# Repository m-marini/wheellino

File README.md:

Wheelly is a wheels robot.

The robot consits of

- Chassis with two lateral wheels driven by 2 x DC motors and a free wheel.
- 2 x IR speed sensors for the wheels
- Motor controller board L298N
- 12V DC rechargable motors Li battery
- 5V DC rechargable controller Li battery
- Power supply module 3.3V
- MPU6050 gyroscope module
- ESP32 Vroom main controller board
- SG90 Microservo
- 2 x Lidar sensors
- 6 x microswitch contact sensors
- LCD Display
- Wifi-Camera

The ESP32 controller is driving all the units to allow the robot to collect the sensor data, compute the position relative the initial state, drive the proxcimity sensor direction, drive the robot for a specific direction and speed by feeding back from gyroscpe and speed sensors and comunicate with remote server via wifi sending status and receiving commands.

Documentation in [Wiki](https://github.com/m-marini/wheellino/wiki)

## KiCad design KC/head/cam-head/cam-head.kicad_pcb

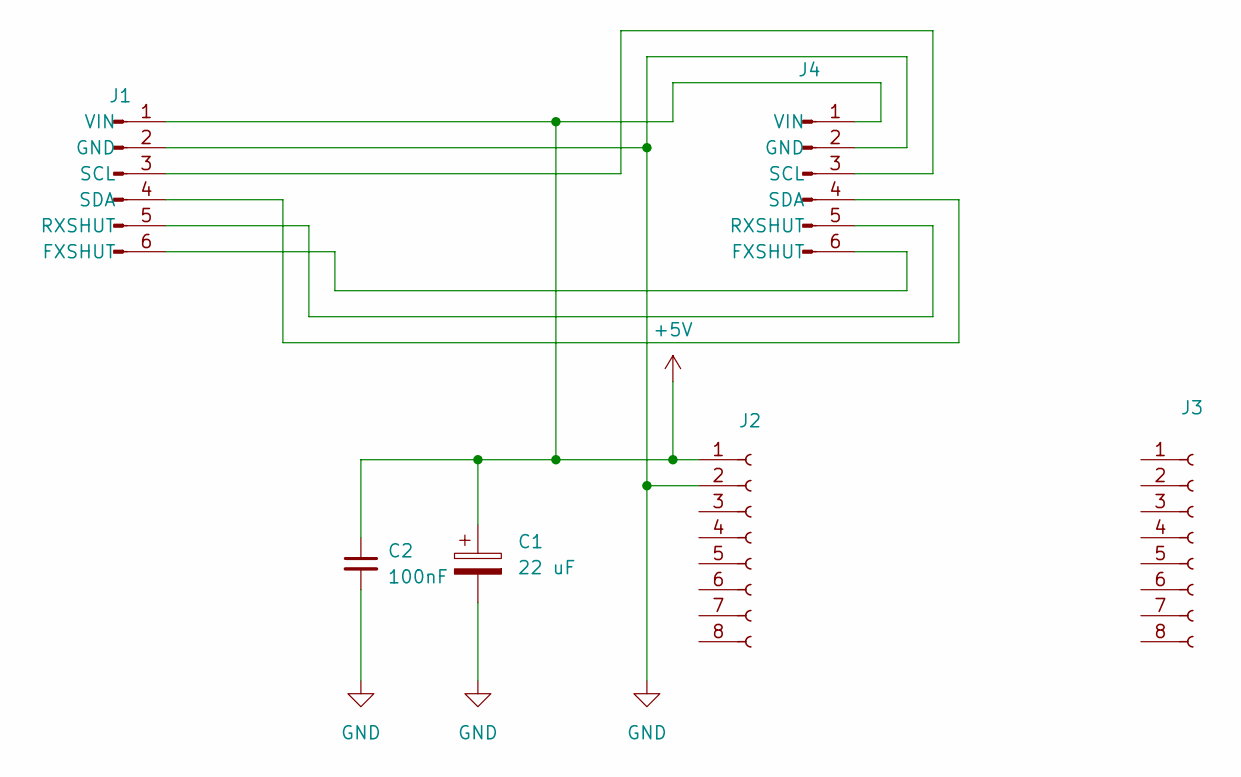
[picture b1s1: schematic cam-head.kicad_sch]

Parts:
C1: 22 uF; CP_Radial_D5.0mm_P2.50mm
C2: 100nF; C_Rect_L7.0mm_W2.5mm_P5.00mm
J1: Conn_01x06_Pin; PinHeader_1x06_P2.54mm_Horizontal
J2, J3: Conn_01x08_Socket; PinSocket_1x08_P2.54mm_Vertical
J4: Conn_01x06_Pin; PinHeader_1x06_P2.54mm_Vertical

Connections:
+5V: C1.1, C2.1, J1.1 (VIN), J2.1, J4.1 (VIN)
GND: C1.2, C2.2, J1.2 (GND), J2.2, J4.2 (GND)
unnamed: J1.6 (FXSHUT), J4.6 (FXSHUT)
unnamed: J1.5 (RXSHUT), J4.5 (RXSHUT)
unnamed: J1.3 (SCL), J4.3 (SCL)
unnamed: J1.4 (SDA), J4.4 (SDA)

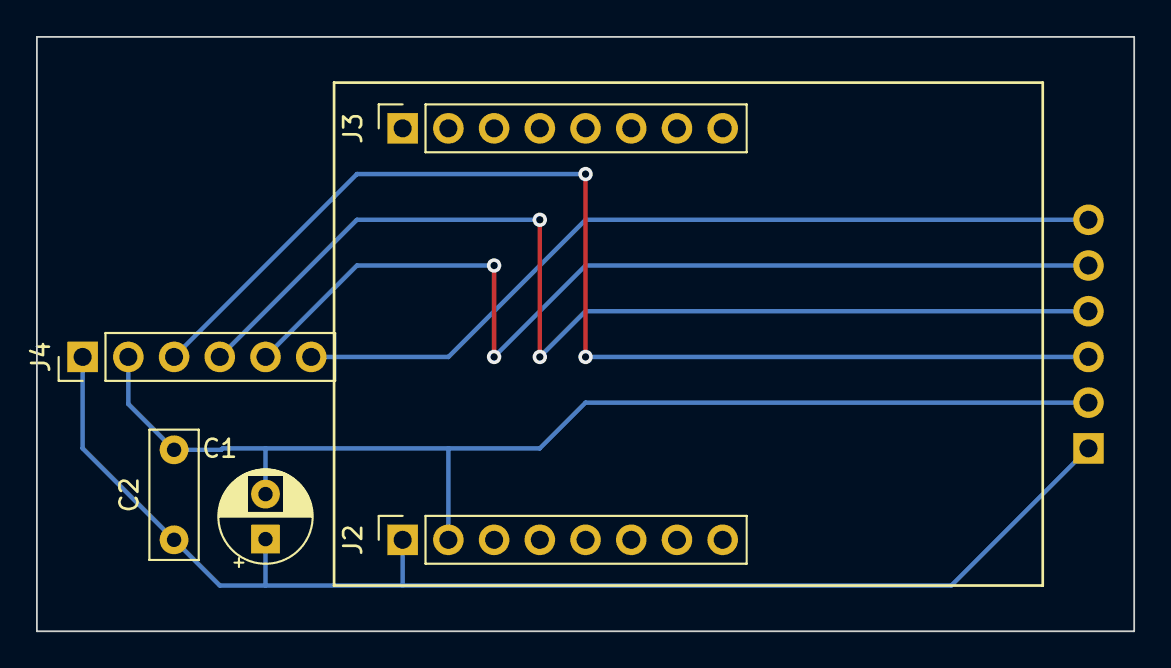
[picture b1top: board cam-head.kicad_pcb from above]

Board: 2 copper layers, 61.0 x 33.0 mm, 6 parts (1 on the bottom side), 6 nets.

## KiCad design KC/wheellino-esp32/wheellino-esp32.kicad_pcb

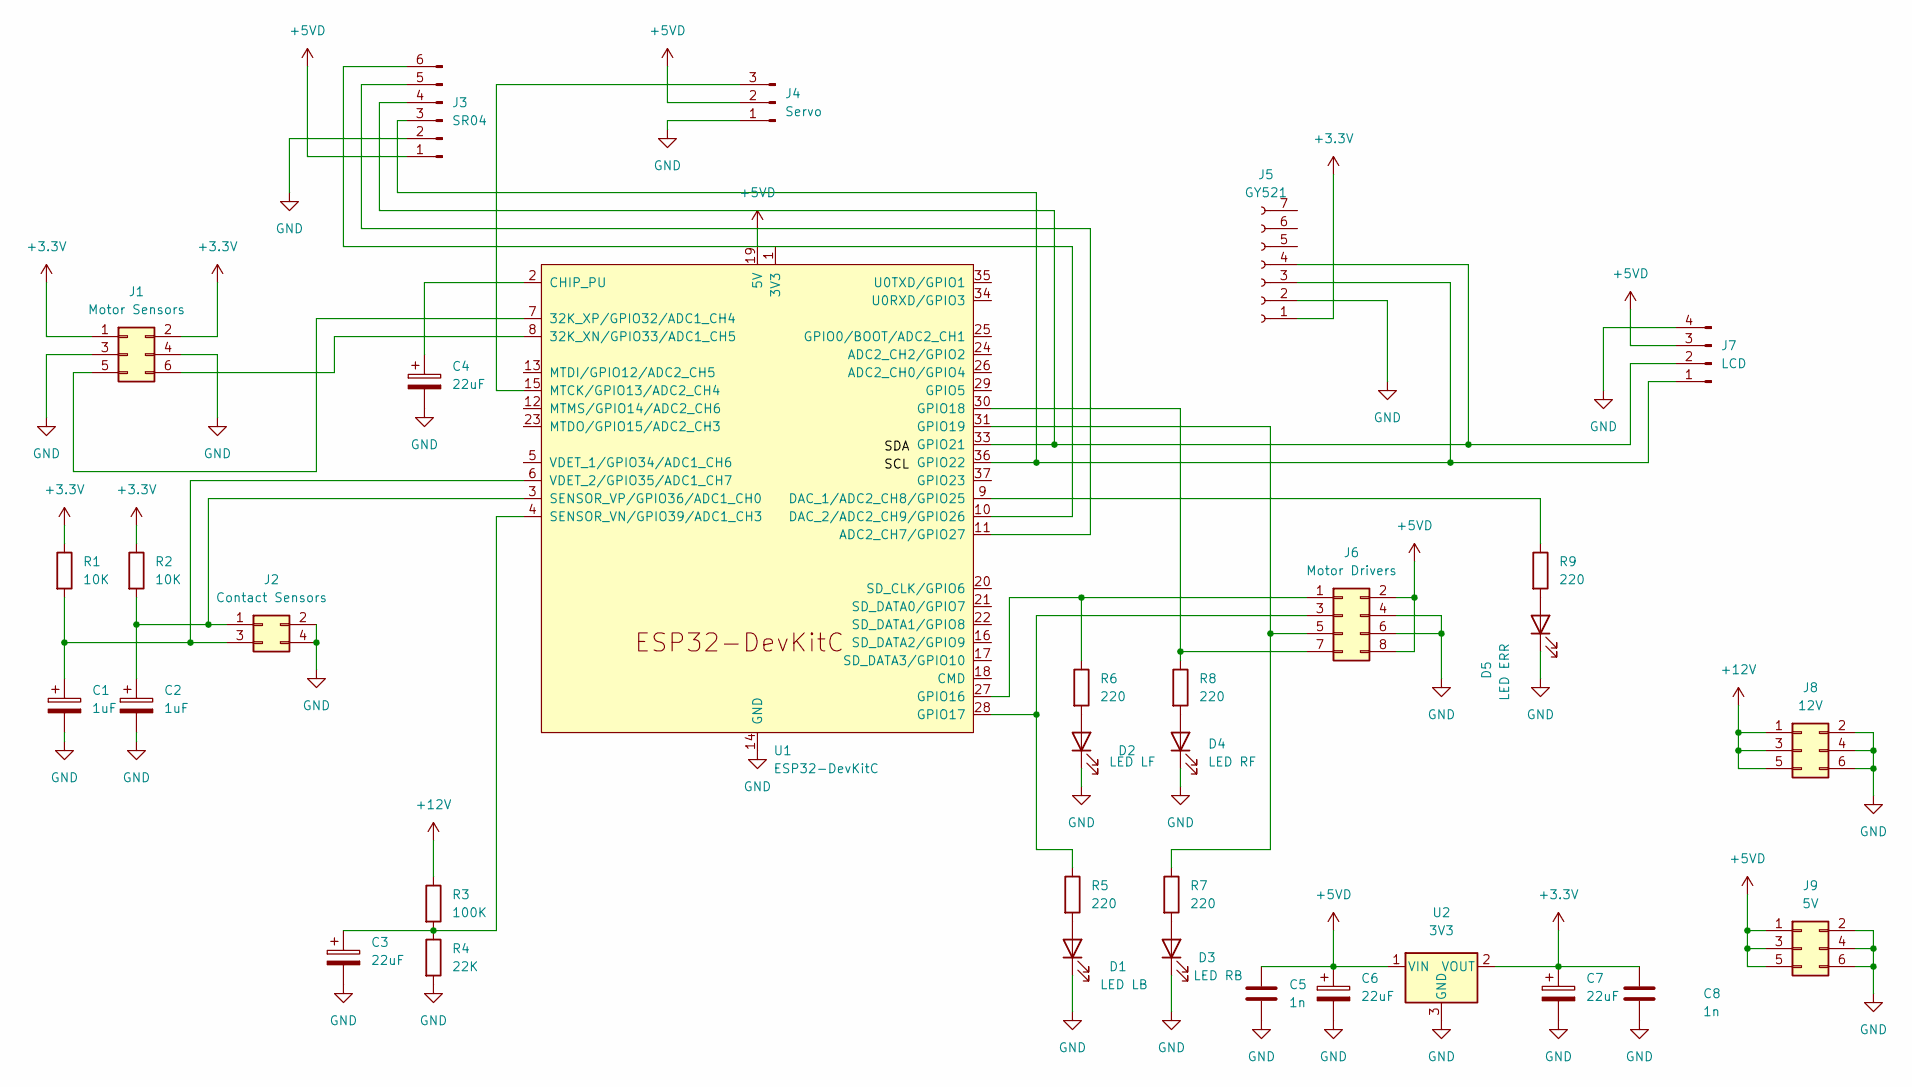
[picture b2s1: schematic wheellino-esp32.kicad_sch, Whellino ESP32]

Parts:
C1, C2: 1uF; CP_Radial_D5.0mm_P2.50mm
C3, C4, C6, C7: 22uF; CP_Radial_D5.0mm_P2.50mm
C5, C8: 1n; C_Rect_L7.0mm_W2.0mm_P5.00mm
D1: LED LB; LED_D5.0mm
D2: LED LF; LED_D5.0mm
D3: LED RB; LED_D5.0mm
D4: LED RF; LED_D5.0mm
D5: LED ERR; LED_D5.0mm
J1: Motor Sensors; PinHeader_2x03_P2.54mm_Vertical
J2: Contact Sensors; PinHeader_2x02_P2.54mm_Vertical
J3: SR04; PinHeader_1x06_P2.54mm_Vertical
J4: Servo; PinHeader_1x03_P2.54mm_Vertical
J5: GY521; PinSocket_1x08_P2.54mm_Vertical
J6: Motor Drivers; PinHeader_2x04_P2.54mm_Vertical
J7: LCD; PinHeader_1x04_P2.54mm_Vertical
J8: 12V; PinHeader_2x03_P2.54mm_Vertical
J9: 5V; PinHeader_2x03_P2.54mm_Vertical
R1, R2: 10K; R_Axial_DIN0207_L6.3mm_D2.5mm_P10.16mm_Horizontal
R3: 100K; R_Axial_DIN0207_L6.3mm_D2.5mm_P10.16mm_Horizontal
R4: 22K; R_Axial_DIN0207_L6.3mm_D2.5mm_P10.16mm_Horizontal
R5, R6, R7, R8, R9: 220; R_Axial_DIN0207_L6.3mm_D2.5mm_P10.16mm_Horizontal
U1: ESP32-DevKitC; ESP32
U2: 3V3; PinHeader_1x03_P2.54mm_Vertical

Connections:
+3V3: C7.1, C8.1, J1.1, J1.2, J5.1, R1.1, R2.1, U2.2 (VOUT)
+12V: J8.1, J8.3, J8.5, R3.1
GND: C1.2, C2.2, C3.2, C4.2, C5.2, C6.2, C7.2, C8.2, D1.1 (K), D2.1 (K), D3.1 (K), D4.1 (K), D5.1 (K), J1.3, J1.4, J2.2, J2.4, J3.2, J4.1, J5.2, J6.4, J6.6, J7.4, J8.2, J8.4, J8.6, J9.2, J9.4, J9.6, R4.2, U1.14 (GND), U1.32 (GND), U1.38 (GND), U2.3 (GND)
unnamed: D1.2 (A), R5.2
unnamed: D2.2 (A), R6.2
unnamed: D3.2 (A), R7.2
unnamed: D4.2 (A), R8.2
unnamed: D5.2 (A), R9.2
unnamed: J1.5, U1.7 (32K_XP/GPIO32/ADC1_CH4)
unnamed: J1.6, U1.8 (32K_XN/GPIO33/ADC1_CH5)
unnamed: C2.1, J2.1, R2.2, U1.3 (SENSOR_VP/GPIO36/ADC1_CH0)
unnamed: C1.1, J2.3, R1.2, U1.6 (VDET_2/GPIO35/ADC1_CH7)
unnamed: J3.3, J5.3, J7.1, U1.36 (GPIO22)
unnamed: J3.4, J5.4, J7.2, U1.33 (GPIO21)
unnamed: J3.6, U1.10 (DAC_2/ADC2_CH9/GPIO26)
unnamed: J4.3, U1.15 (MTCK/GPIO13/ADC2_CH4)
unnamed: J6.1, R6.1, U1.27 (GPIO16)
unnamed: J6.3, R5.1, U1.28 (GPIO17)
unnamed: J6.5, R7.1, U1.31 (GPIO19)
unnamed: J6.7, R8.1, U1.30 (GPIO18)
unnamed: C4.1, U1.2 (CHIP_PU)
unnamed: R9.1, U1.9 (DAC_1/ADC2_CH8/GPIO25)
unnamed: C3.1, R3.2, R4.1, U1.4 (SENSOR_VN/GPIO39/ADC1_CH3)

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
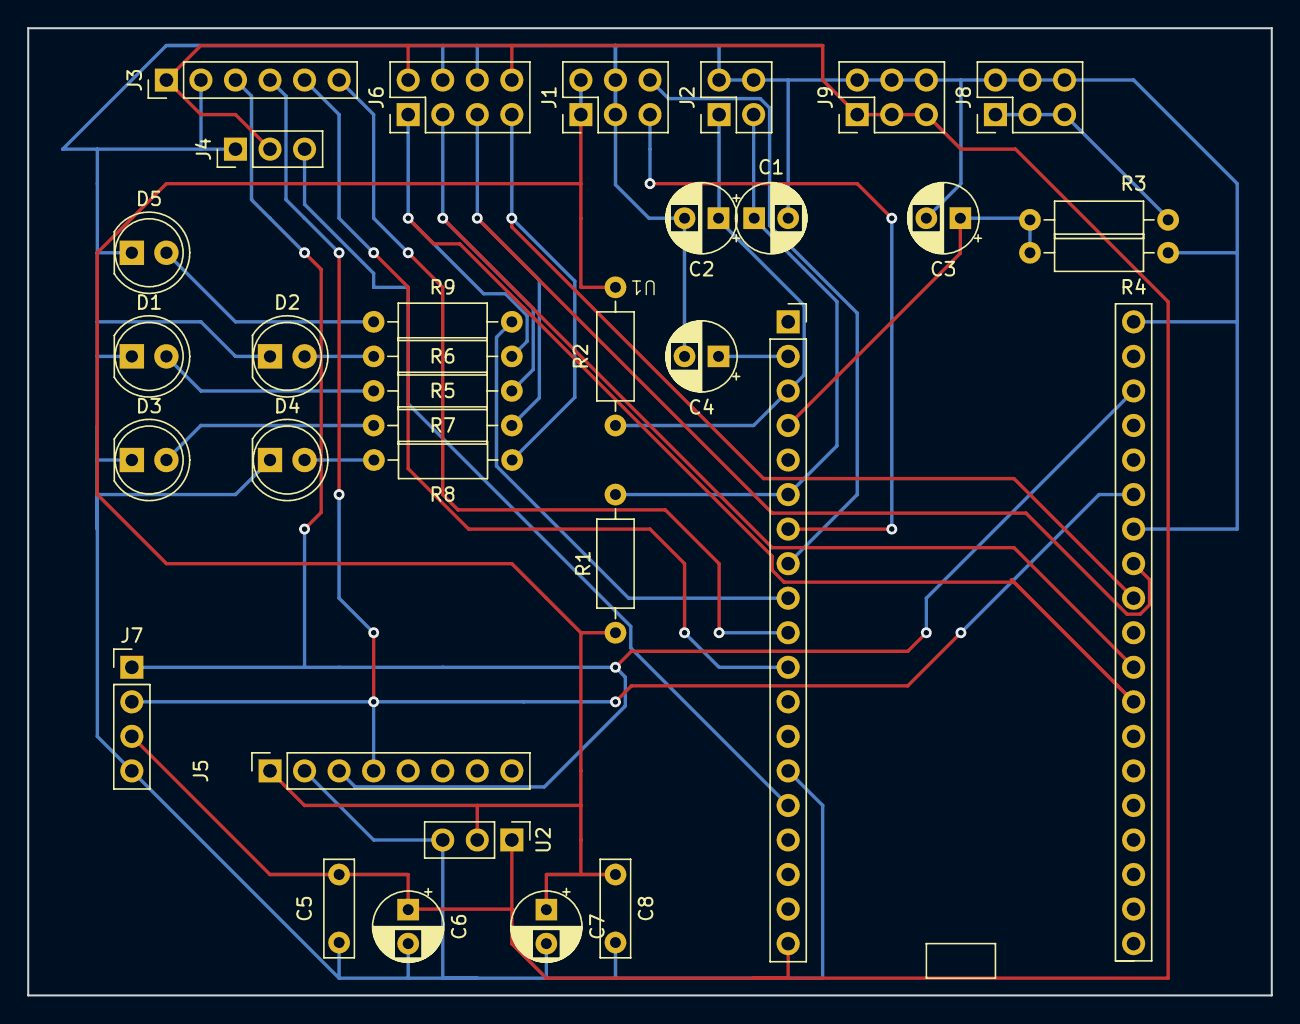
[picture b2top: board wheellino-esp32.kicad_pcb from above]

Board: 2 copper layers, 91.4 x 71.1 mm, 33 parts (0 on the bottom side), 25 nets.

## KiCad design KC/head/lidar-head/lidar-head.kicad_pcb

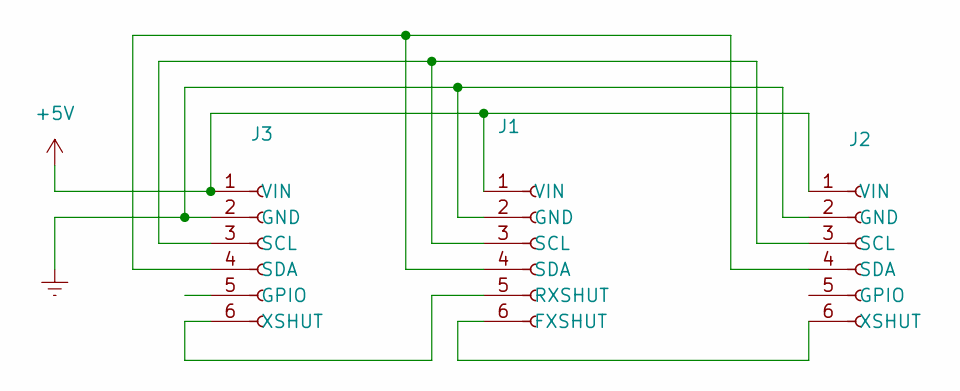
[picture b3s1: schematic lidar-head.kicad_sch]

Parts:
J1, J2, J3: Conn_01x06_Socket; PinSocket_1x06_P2.54mm_Vertical

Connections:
+5V: J1.1 (VIN), J2.1 (VIN), J3.1 (VIN)
Earth: J1.2 (GND), J2.2 (GND), J3.2 (GND)
unnamed: J1.6 (FXSHUT), J2.6 (XSHUT)
unnamed: J1.5 (RXSHUT), J3.6 (XSHUT)
unnamed: J1.3 (SCL), J2.3 (SCL), J3.3 (SCL)
unnamed: J1.4 (SDA), J2.4 (SDA), J3.4 (SDA)

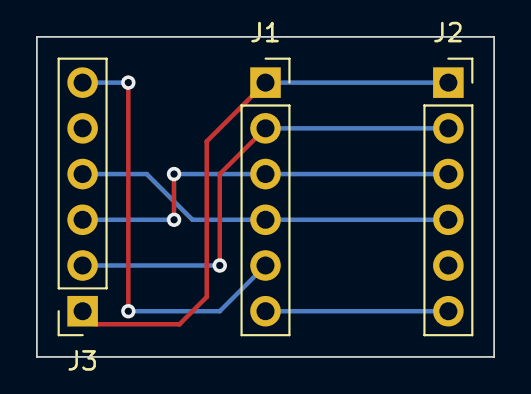
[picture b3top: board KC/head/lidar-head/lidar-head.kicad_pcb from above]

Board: 2 copper layers, 25.4 x 17.8 mm, 3 parts (0 on the bottom side), 6 nets.

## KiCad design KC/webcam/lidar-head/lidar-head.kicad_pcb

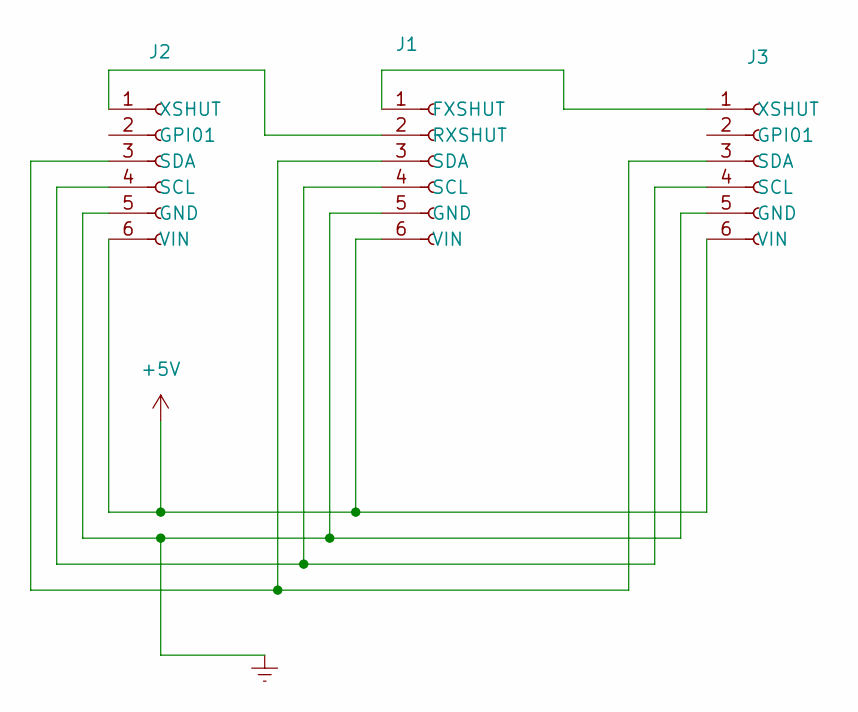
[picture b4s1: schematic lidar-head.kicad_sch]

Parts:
J1, J2, J3: Conn_01x06_Socket; PinSocket_1x06_P2.54mm_Vertical

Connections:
+5V: J1.6, J2.6 (VIN), J3.6 (VIN)
Earth: J1.5, J2.5 (GND), J3.5 (GND)
unnamed: J1.1, J3.1 (XSHUT)
unnamed: J1.2, J2.1 (XSHUT)
unnamed: J1.3, J2.3 (SDA), J3.3 (SDA)
unnamed: J1.4, J2.4 (SCL), J3.4 (SCL)

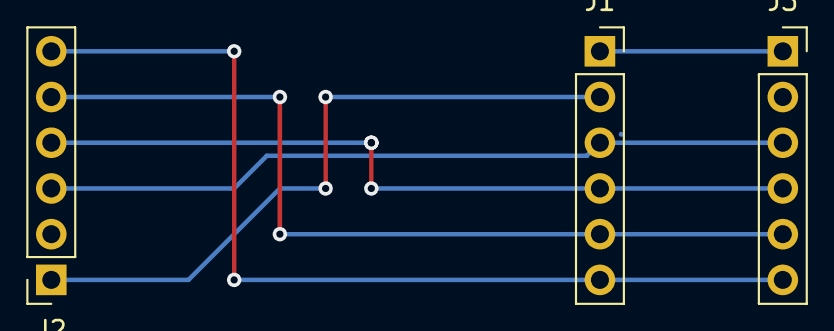
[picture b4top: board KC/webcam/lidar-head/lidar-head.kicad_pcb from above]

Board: 2 copper layers, 3 parts (0 on the bottom side), 6 nets.

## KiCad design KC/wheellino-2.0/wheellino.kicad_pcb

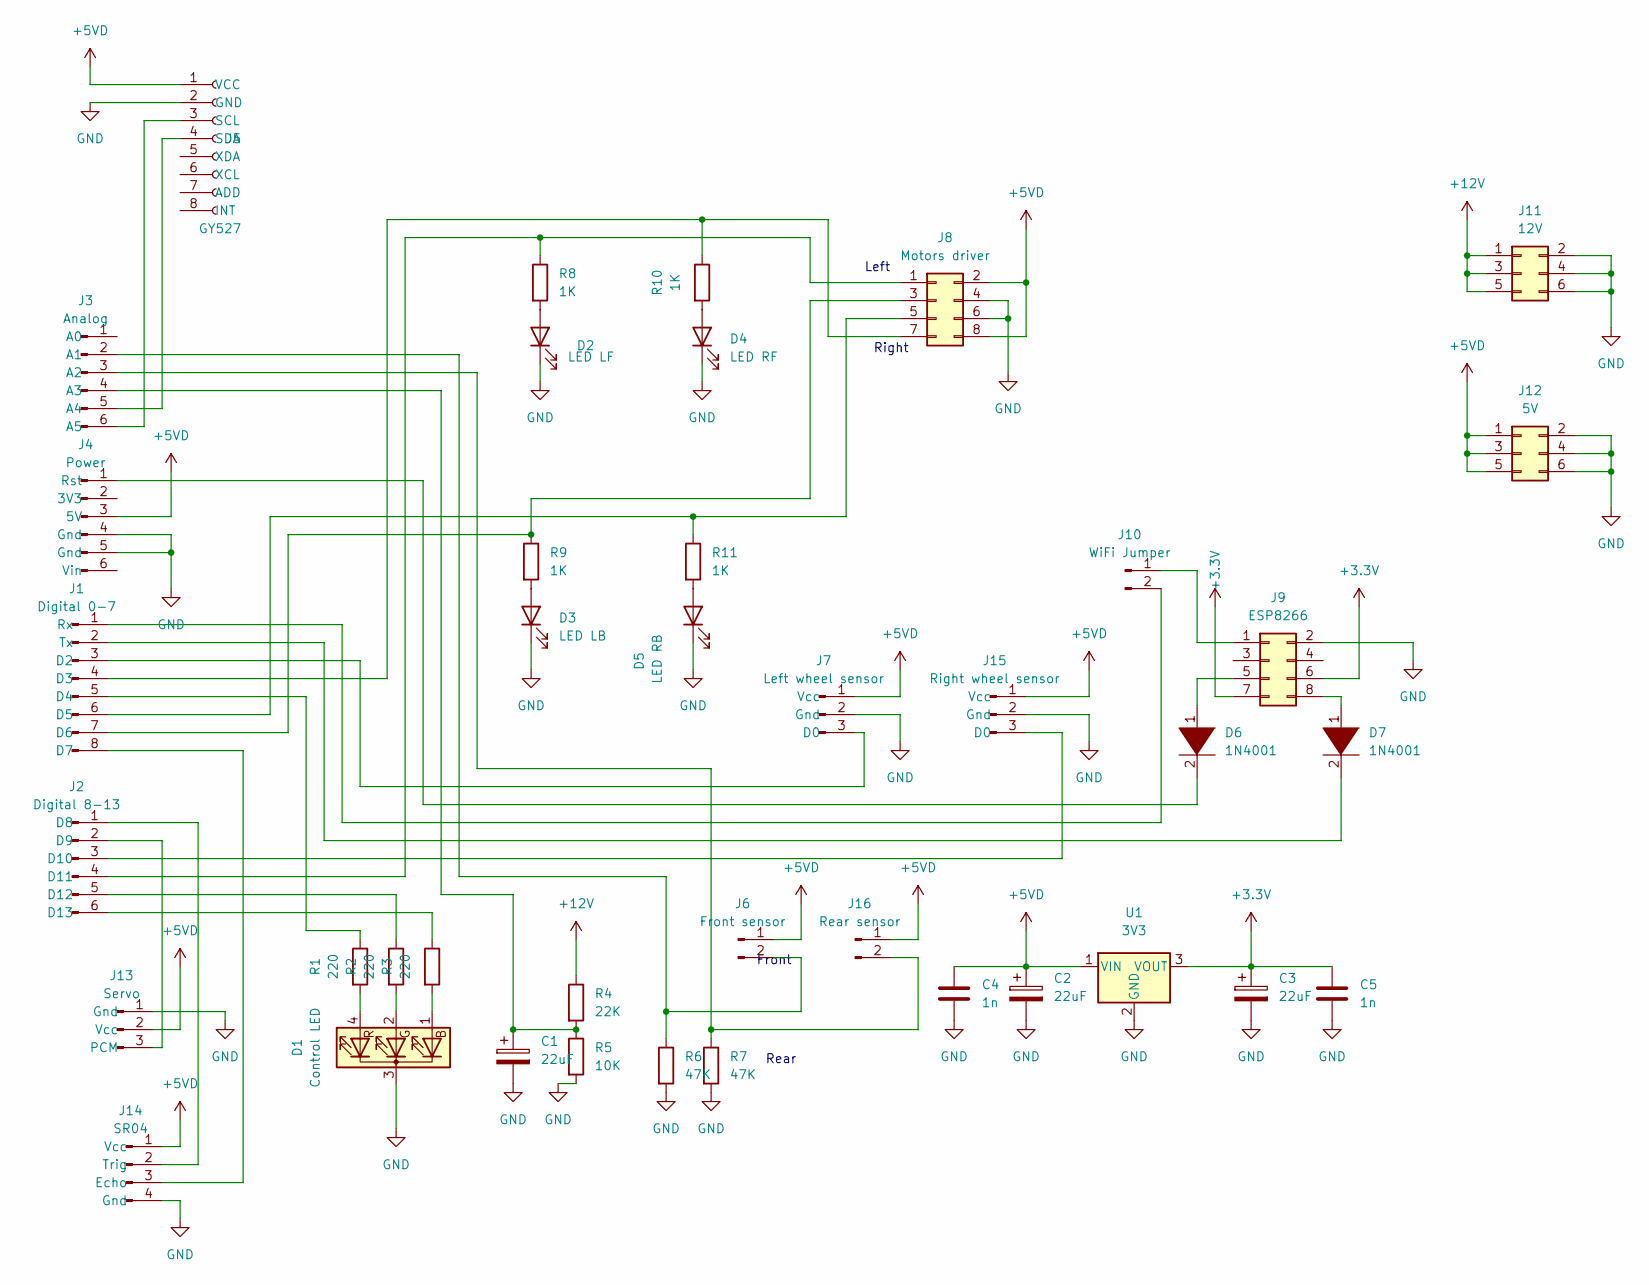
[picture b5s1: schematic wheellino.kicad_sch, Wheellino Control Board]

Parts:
C1, C2, C3: 22uF; CP_Radial_D5.0mm_P2.50mm
C4, C5: 1n; C_Rect_L7.0mm_W2.0mm_P5.00mm
D1: Control LED; LED_D5.0mm-4_RGB_Wide_Pins
D2: LED LF; LED_D5.0mm
D3: LED LB; LED_D5.0mm
D4: LED RF; LED_D5.0mm
D5: LED RB; LED_D5.0mm
D6, D7: 1N4001; D_DO-41_SOD81_P10.16mm_Horizontal
J1: Digital 0-7; PinHeader_1x08_P2.54mm_Vertical
J2: Digital 8-13; PinHeader_1x06_P2.54mm_Vertical
J3: Analog; PinHeader_1x06_P2.54mm_Vertical
J4: Power; PinHeader_1x06_P2.54mm_Vertical
J5: GY527; PinSocket_1x08_P2.54mm_Vertical
J6: Front sensor; PinHeader_1x02_P2.54mm_Vertical
J7: Left wheel sensor; PinHeader_1x03_P2.54mm_Vertical
J8: Motors driver; PinHeader_2x04_P2.54mm_Vertical
J9: ESP8266; PinHeader_2x04_P2.54mm_Vertical
J10: WiFi Jumper; PinHeader_1x02_P2.54mm_Vertical
J11: 12V; PinHeader_2x03_P2.54mm_Vertical
J12: 5V; PinHeader_2x03_P2.54mm_Vertical
J13: Servo; PinHeader_1x03_P2.54mm_Vertical
J14: SR04; PinHeader_1x04_P2.54mm_Vertical
J15: Right wheel sensor; PinHeader_1x03_P2.54mm_Vertical
J16: Rear sensor; PinHeader_1x02_P2.54mm_Vertical
R1, R2, R3: 220; R_Axial_DIN0207_L6.3mm_D2.5mm_P10.16mm_Horizontal
R4: 22K; R_Axial_DIN0207_L6.3mm_D2.5mm_P10.16mm_Horizontal
R5: 10K; R_Axial_DIN0207_L6.3mm_D2.5mm_P10.16mm_Horizontal
R6, R7: 47K; R_Axial_DIN0207_L6.3mm_D2.5mm_P10.16mm_Horizontal
R8, R9, R10, R11: 1K; R_Axial_DIN0207_L6.3mm_D2.5mm_P10.16mm_Horizontal
U1: 3V3; PinHeader_1x03_P2.54mm_Vertical

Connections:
+3V3: C3.1, C5.1, J9.6, J9.7, U1.3 (VOUT)
+5VD: C2.1, C4.1, J4.3 (5V), J5.1 (VCC), J6.1, J7.1 (Vcc), J8.2, J8.8, J12.1, J12.3, J12.5, J13.2 (Vcc), J14.1 (Vcc), J15.1 (Vcc), J16.1, U1.1 (VIN)
+12V: J11.1, J11.3, J11.5, R4.1
GND: C1.2, C2.2, C3.2, C4.2, C5.2, D1.3 (K), D2.1 (K), D3.1 (K), D4.1 (K), D5.1 (K), J4.4 (Gnd), J4.5 (Gnd), J5.2 (GND), J7.2 (Gnd), J8.4, J8.6, J9.2, J11.2, J11.4, J11.6, J12.2, J12.4, J12.6, J13.1 (Gnd), J14.4 (Gnd), J15.2 (Gnd), R5.2, R6.2, R7.2, U1.2 (GND)
unnamed: C1.1, J3.4 (A3), R4.2, R5.1
unnamed: D1.1 (BA), R3.2
unnamed: D1.2 (GA), R2.2
unnamed: D1.4 (RA), R1.2
unnamed: D2.2 (A), R8.2
unnamed: D3.2 (A), R9.2
unnamed: D4.2 (A), R10.2
unnamed: D5.2 (A), R11.2
unnamed: D6.1 (K), J9.5
unnamed: D6.2 (A), J4.1 (Rst)
unnamed: D7.1 (K), J9.8
unnamed: D7.2 (A), J1.2 (Tx)
unnamed: J1.1 (Rx), J10.2
unnamed: J1.3 (D2), J7.3 (D0)
unnamed: J1.4 (D3), J8.7, R10.1
unnamed: J1.5 (D4), R1.1
unnamed: J1.6 (D5), J8.5, R11.1
unnamed: J1.7 (D6), J8.3, R9.1
unnamed: J1.8 (D7), J14.3 (Echo)
unnamed: J2.4 (D11), J8.1, R8.1
unnamed: J2.5 (D12), R2.1
unnamed: J2.6 (D13), R3.1
unnamed: J3.2 (A1), J6.2, R6.1
unnamed: J3.3 (A2), J16.2, R7.1
unnamed: J3.5 (A4), J5.4 (SDA)
unnamed: J3.6 (A5), J5.3 (SCL)
unnamed: J9.1, J10.1
unnamed: J2.2 (D9), J13.3 (PCM)
unnamed: J2.1 (D8), J14.2 (Trig)
unnamed: J2.3 (D10), J15.3 (D0)

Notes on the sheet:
Rear
Left
Front
Right

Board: 2 copper layers, 40 parts (0 on the bottom side), 34 nets, no tracks yet.

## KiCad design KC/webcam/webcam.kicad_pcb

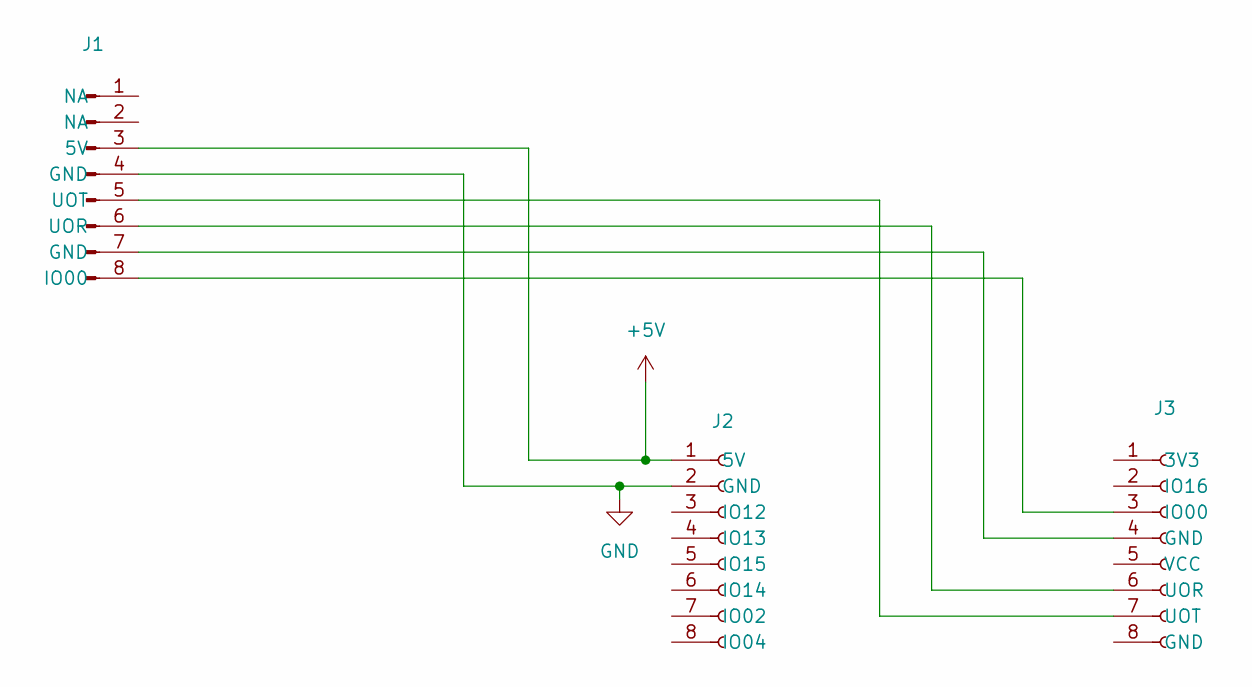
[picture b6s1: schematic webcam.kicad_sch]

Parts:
J1: Conn_01x08_Pin; PinHeader_1x08_P2.54mm_Horizontal
J2, J3: Conn_01x08_Socket; PinSocket_1x08_P2.54mm_Vertical

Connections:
+5V: J1.3 (5V), J2.1 (5V)
GND: J1.4 (GND), J2.2 (GND)
unnamed: J1.7 (GND), J3.4 (GND)
unnamed: J1.8 (IO00), J3.3 (IO00)
unnamed: J1.6 (UOR), J3.6 (UOR)
unnamed: J1.5 (UOT), J3.7 (UOT)

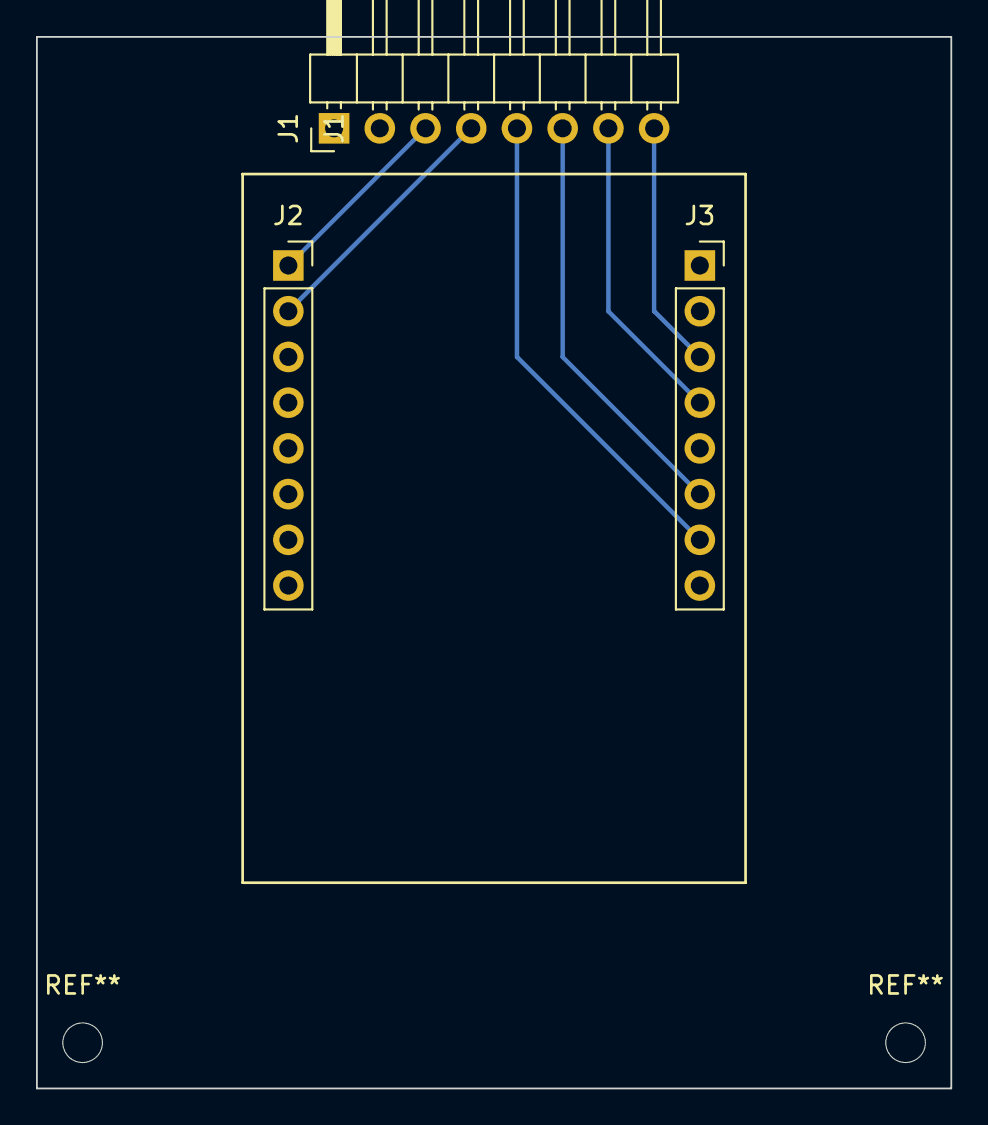
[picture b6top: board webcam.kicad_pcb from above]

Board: 2 copper layers, 50.8 x 58.4 mm, 3 parts (0 on the bottom side), 6 nets.

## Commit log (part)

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2022-06-17 issue #1
2022-06-17 fixed readme
2022-06-18 Imported KC folder
2022-07-14 Changed startup led sequence and output wifi IP Address #5
2022-07-16 Standard reference system #7
2022-08-14 Issue#9: MPU failure bug
2022-08-14 changelog
2022-09-12 Issue #1: status led for default access point
2022-09-12 Add GET network configuration api #13
2022-12-17 Issue #16: Add movement check up
2023-01-01 Squashed commit of the following:
    commit 675f6ed85ed7138b55e524eea166590810c414db
    Author: mmarini <marco.marini@mmarini.org>
    Date: Sun Jan 1 23:26:21 2023 +0100
    changelog
    commit d4c45f285577b641f5c4358d7b80246b7f26a76f
    Author: mmarini <marco.marini@mmarini.org>
2023-01-08 Motor configuration command integer motor power minimal conversion location and speed sensor minimal conversion of contact sensors minimal conversion of distance, voltage
2023-01-17 Change WheellyMeasures #22
2023-01-20 motor supply at 12V and configuration command
2023-01-20 Change motor power supply and add controller configurations
2023-01-21 Configuration command error #27
2023-02-07 Set contact sensors thresholds
2023-02-07 Issue #32: Limit robot angular speed
2023-02-09 Issue #34: Change WheellyMeasures to run ramp power measures
2023-02-10 Managing stiction in motor controller
2023-02-11 Issue #36: Change motor controller to manage stiction
2023-02-11 issue #38 error at cl command
2023-02-11 Issue #40: Error parsing cm command
2023-02-12 Issue #42: Merge filter and speedmeter
2023-02-12 Issue #44: Add power acceleration limits
2023-02-22 Added bland and new base
2023-02-24 Blender model
2023-08-08 Command interpreter esp32 and tests wheellino-2.0 Changed base
2023-08-10 Esp32 board
2023-08-20 Changed
2023-08-20 reordered
2023-08-22 Fixed pcb error
2023-10-10 Issue #61: Bug Wifi post config dump
2023-10-11 API get networks list often run in Guru meditation #64
2023-10-13 snapshot
2023-10-13 Issue #55: Add configure proxy scan interval
2023-10-16 yaw drift
2023-10-16 Issue #69: Add physic measures
2023-10-17 Issue #71: Change measures with power ramp up and down
2023-10-17 Issue #73: Fix report with start and stop test records
2023-10-20 Issue #75: Change motion by mixing rotation and movement
2023-10-20 Issue #78: Add friction test
2023-10-22 #80: Change stiction and friction test
2023-10-22 Remove arduino one board code #82
2023-10-31 Issue #84: Add battery level icons
2023-11-07 Issue #86: Add proxy sensor noise filter
2023-11-12 #88: Fix status send frequence on move (TCS review)
2023-11-14 Issue #91: Change LED status flashing
2023-11-17 Issue #93: Switch on LED utill start
2023-11-17 fix version
2023-12-05 ProxySensor
2023-12-05 #95: Unexpetcted restart on servo movement
2023-12-11 smooth servo new comamnd interpreter async status messages
2023-12-11 Added string command
2023-12-11 changed log
2023-12-14 Issue #98: Add asyncronous status messages
2023-12-14 updated changelog
2023-12-28 Averaging supply measures #104
2024-08-22 Add web camera #107
2025-06-29 flashing cam LED
2025-07-17 esp32 board 3.2.1
2025-08-12 Mqtt client and ConfStore
2025-08-12 Api server ConfStore WiFiModule
2025-08-13 version 0.9.0
2025-08-15 iot topics design
2025-08-15 wheelly mqtt completed
2025-08-24 morse led signal mqtt camera, esp log, cvs arguments MQTT CameraDevice sketch iot topics design
2025-10-06 Add lidar
2025-10-06 Lidar
2025-10-10 head cad projects
2025-11-06 flip camera image Lidar signals LidarServo head cad projects Add lidar
2025-12-22 changed motor controller
2025-12-23 Mqtt Wheelly measures
2025-12-24 Delay test end
2025-12-26 Optimeze messages
2025-12-27 Added lidars and changed parameters validation
2025-12-29 Add supply measure
2026-01-01 Wheelly measures
2026-01-01 Motor fix
2026-01-17 Add SD Camera Card and change motor controller by voltage
2026-02-08 add head rotasion limits and changed servo controller
2026-02-26 Update CHANGELOG for version 0.10.0
    Added new version 0.10.0 with Lidar sensors and test record.
2026-03-03 motor controlled by pulse width go commands
2026-03-07 cf and qc command
2026-03-07 Update CHANGELOG with new issue references
2026-03-07 Fix issue links in CHANGELOG.md
2026-03-08 fixed
